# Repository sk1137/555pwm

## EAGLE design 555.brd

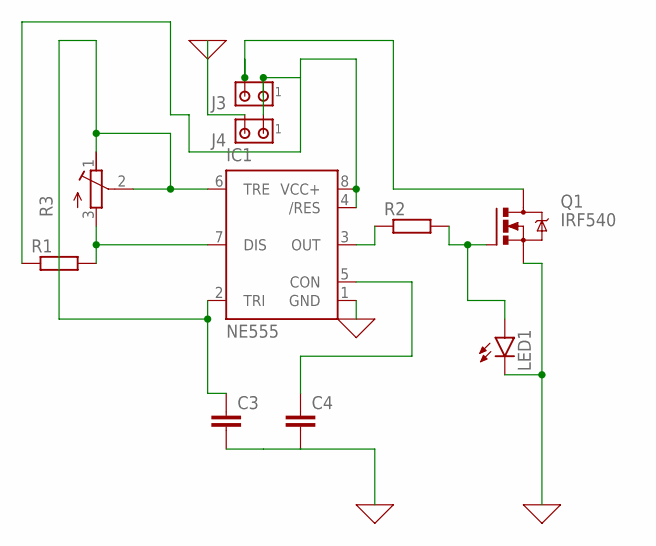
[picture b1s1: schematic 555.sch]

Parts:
C3, C4: C2.5/5; C2.5-5
IC1: NE555; DIL-08
J3, J4: MTA02-100; 10X02MTA
LED1: LEDSQR2X5; LED2X5
Q1: IRF540; TO220BV
R1: R-EU_0204/5; 0204/5
R2: R-EU_0207/7; 0207/7
R3: R-TRIMMT93XA; RTRIMT93XA

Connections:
0: C3.2, C4.2, IC1.1 (GND), J4.2, LED1.K (C), Q1.S
unnamed: IC1.3 (OUT), R2.1
unnamed: IC1.4 (/RES), IC1.8 (VCC+), J3.1, J4.1, R1.1
unnamed: LED1.A, Q1.G, R2.2
unnamed: C3.1, IC1.2 (TRI), IC1.6 (TRE), R3.1 (E), R3.2 (S)
unnamed: IC1.7 (DIS), R1.2, R3.3 (A)
unnamed: C4.1, IC1.5 (CON)
unnamed: J3.2, Q1.D

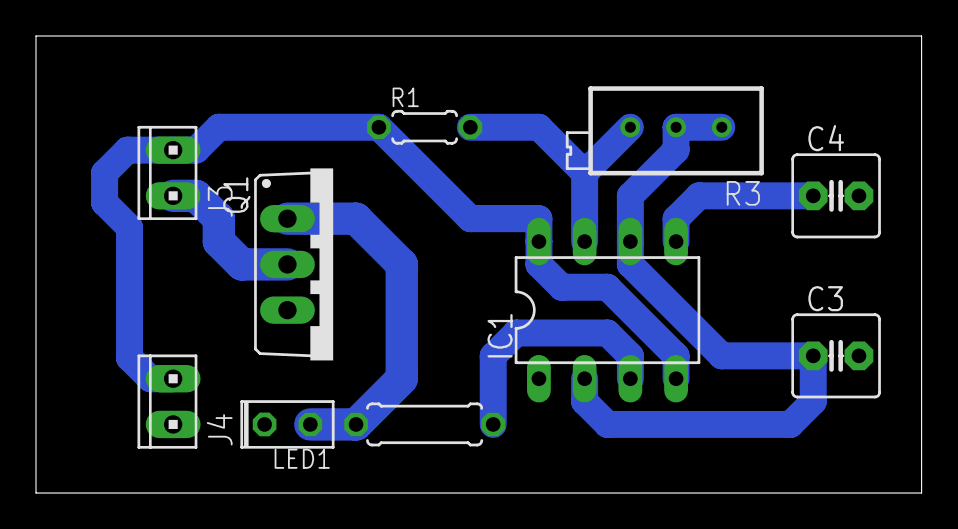
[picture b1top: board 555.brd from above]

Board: 2 copper layers, 49.2 x 25.4 mm, 10 parts (0 on the bottom side), 8 nets.
